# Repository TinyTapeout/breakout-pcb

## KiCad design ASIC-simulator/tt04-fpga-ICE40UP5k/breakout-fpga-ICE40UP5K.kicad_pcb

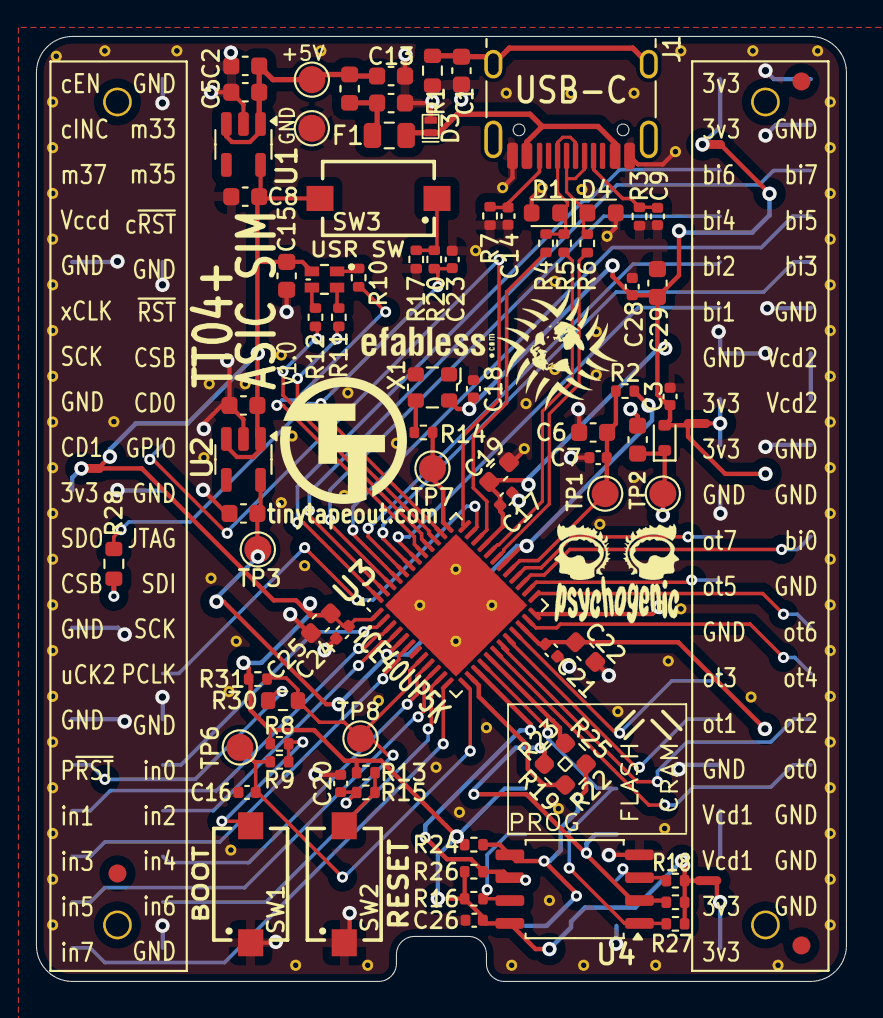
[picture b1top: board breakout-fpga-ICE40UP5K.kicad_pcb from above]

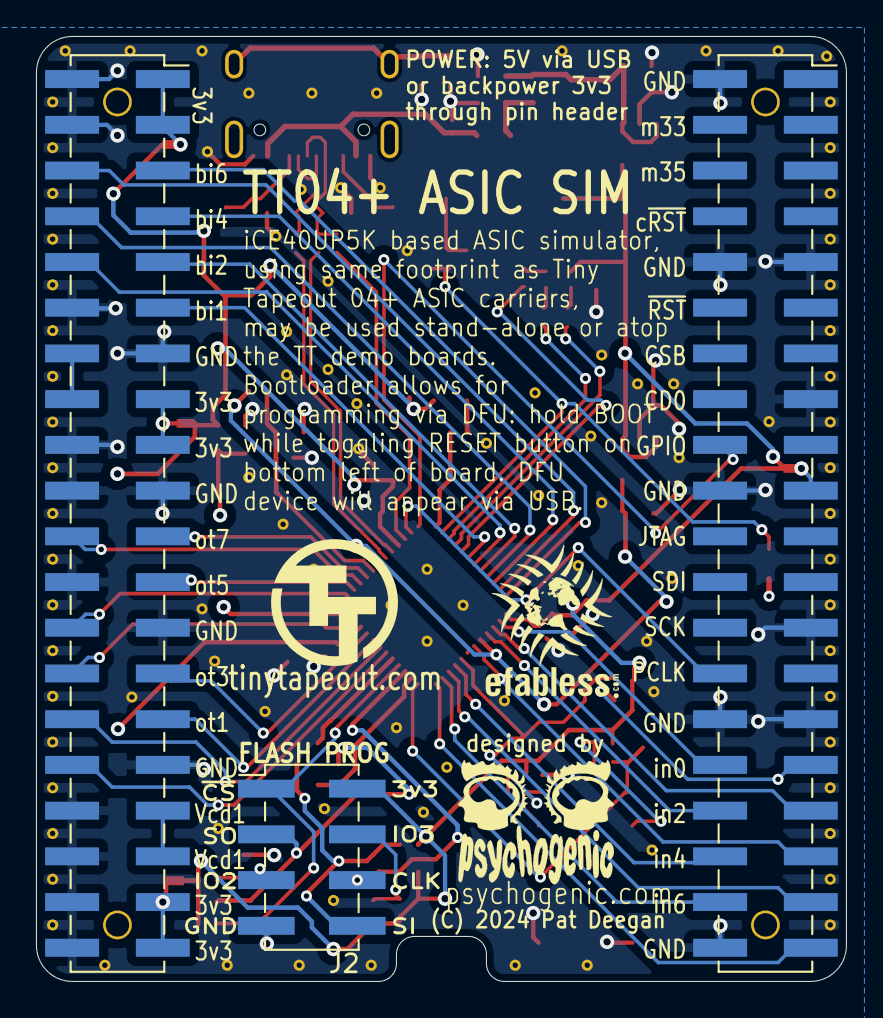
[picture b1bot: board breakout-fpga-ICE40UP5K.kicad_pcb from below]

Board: 4 copper layers, 45.0 x 52.5 mm, 191 parts (3 on the bottom side), 71 nets.

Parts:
C1: CUSBSHIELD; C_0603_1608Metric
C2, C4, C5, C8, C11, C12, C13: C_1u_0603_50V; C_0603_1608Metric
C3, C7, C16, C17, C18, C20, C21, C23, C24, C26, C28: C_100n_0402_50V; C_0402_1005Metric
C6, C10, C15, C19, C22, C25, C29: C_4p7u_0603_25V; C_0603_1608Metric
C9, C14: C_330p_0402_50V; C_0402_1005Metric
CON1, CON2: FH-00148_PinSocket_2x20_P2.54mm
D1, D4: TVS; D_0603_1608Metric
D2: 1N4448WT; D_SOD-523
D3: VBUSTVS; DFN1006-2
D5: RGB; LED_EAST1616RGBA3
F1: 350mA; Fuse_0805_2012Metric
FB1: 120R; L_0603_1608Metric
FID1, FID2, FID3: Fiducial; Fiducial_1mm_Mask2mm
J1: USB_C; USB_C_Receptacle_HRO_TYPE-C-31-M-12
J2: Conn_02x04_Odd_Even; PinHeader_2x04_P2.54mm_Vertical_SMD
NT1, NT2, NT3, NT4: NetTie_2; NetTie-2_SMD_Pad0.5mm
R1: R_1M_0603; R_0603_1608Metric
R2, R10, R14: R_100R_0402; R_0402_1005Metric
R3, R7: R_5k1_0402; R_0402_1005Metric
R4, R9, R15, R20: R_1k5_0402; R_0402_1005Metric
R5, R6, R11, R12: R_68R_0402; R_0402_1005Metric
R8, R13, R16, R17, R18, R21, R24, R26, R27, R31: R_10k_0402; R_0402_1005Metric
R19, R22, R23, R25, R28, R30: R_0R_0603_JUMPER; R_0603_1608Metric
STITCH1, STITCH1#2, STITCH1#3, STITCH1#4, STITCH1#5, STITCH1#6, STITCH1#7, STITCH1#8, STITCH1#9, STITCH1#10, STITCH1#11, STITCH1#12, STITCH1#13, STITCH1#14, STITCH1#15, STITCH1#16, STITCH1#17, STITCH1#18, STITCH1#19, STITCH1#20, STITCH1#21, STITCH1#22, STITCH1#23, STITCH1#24, STITCH1#25, STITCH1#26, STITCH1#27, STITCH1#28, STITCH1#29, STITCH1#30, STITCH1#31, STITCH1#32, STITCH1#33, STITCH1#34, STITCH1#35, STITCH1#36, STITCH1#37, STITCH1#38, STITCH1#39, STITCH1#40, STITCH1#41, STITCH1#42, STITCH1#43, STITCH1#44, STITCH2, STITCH3, STITCH4, STITCH5, STITCH6, STITCH7, STITCH8, STITCH9, STITCH10, STITCH11, STITCH12, STITCH13, STITCH14, STITCH15, STITCH17, STITCH18, STITCH19, STITCH20, STITCH21, STITCH22, STITCH23, STITCH24, STITCH25, STITCH26, STITCH27, STITCH28, STITCH29, STITCH30, STITCH31, STITCH32, STITCH33, STITCH34, STITCH35, STITCH36, STITCH37, STITCH38, STITCH39, STITCH40, STITCH43, STITCH44, STITCH46, STITCH47, STITCH48, STITCH50, STITCH51, STITCH52, STITCH54, STITCH59, STITCH60, STITCH61, STITCH62, STITCH62#2, STITCH62#3, STITCH62#4, STITCH62#5: StitchingVia-0.3mm
SW1, SW2, SW3: 434121025816
TP1, TP2, TP3, TP4, TP5, TP6, TP7, TP8: TestPoint; TestPoint_Pad_D1.5mm
U1: AP2112K-3.3; SOT-23-5
U2: AP2112K-1.2; SOT-23-5
U3: ICE40UP5K-SG48ITR; QFN-48-1EP_7x7mm_P0.5mm_EP5.6x5.6mm
U4: W25Q32JVSS; SOIC-8_5.23x5.23mm_P1.27mm
X1: 24MHz; Oscillator_SMD_ECS_2520MV-xxx-xx-4Pin_2.5x2.0mm

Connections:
+1V2: C11.1, R2.1, TP3.1, U2.5 (VOUT), U3.5 (VCC), U3.30 (VCC)
+2V5: C10.1, D2.1 (K), TP2.1, U3.24 (VPP_2V5)
+3V3: C3.1, C4.1, C8.1, C15.1, C17.1, C18.1, C19.1, C21.1, C22.1, C24.1, C25.1, C26.1, C28.1, C29.1, D2.2 (A), D5.4, J2.2, NT1.2, NT2.2, NT3.2, NT4.2, R8.1, R13.1, R16.1, R18.1, R21.1, R24.1, R26.1, R27.1, R31.1, SW3.2, U1.5 (VOUT), U2.1 (VIN), U2.3 (EN), U3.1 (VCCIO_2), U3.22 (SPI_VCCIO1), U3.33 (VCCIO_0), U4.8 (VCC), X1.4 (VDD)
+5V: C2.1, C5.1, C13.1, FB1.2, TP4.1, U1.1 (VIN), U1.3 (EN)
/CC1: C9.1, J1.A5 (CC1), R3.1
/CC2: C14.1, J1.B5 (CC2), R7.1
/FL_MISO: J2.3, R19.1, R21.2, R23.1, U4.2 (DO(IO1))
/FL_MOSI: J2.8, R22.2, R24.2, R25.2, U4.5 (DI(IO0))
/FPGA_SI: R23.2, R25.1, U3.17 (IOB_33b_SPI_SI)
/FPGA_SO: R19.2, R22.1, U3.14 (IOB_32a_SPI_SO)
/IOT_44B: R4.1, U3.34 (IOT_44b)
/LED_B: R12.2, U3.40 (RGB1)
/LED_G: R11.2, U3.39 (RGB0)
/LED_R: R10.2, U3.41 (RGB2)
/VCC_PLL: C6.1, C7.1, R2.2, TP1.1, U3.29 (VCCPLL)
/fl_io2: J2.5, R18.2, U4.3 (IO2)
/fl_io3: J2.4, R16.2, U4.7 (IO3)
/oscclk: R14.1, X1.3 (OUT)
/spi_clk: J2.6, R26.2, U3.15 (IOB_34a_SPI_SCK), U4.6 (CLK)
/vbus: D3.1 (K), F1.1, J1.A4 (VBUS), J1.A9 (VBUS), J1.B4 (VBUS), J1.B9 (VBUS)
/vbusfused: C12.1, F1.2, FB1.1
/~FLCS: J2.1, R27.2, U3.16 (IOB_35b_SPI_SS), U4.1 (~CS)
BOOT: C16.1, R9.2, TP6.1, U3.13 (IOB_24a)
GND: C1.2, C2.2, C3.2, C4.2, C5.2, C6.2, C7.2, C8.2, C9.2, C10.2, C11.2, C12.2, C13.2, C14.2, C15.2, C16.2, C17.2, C18.2, C19.2, C20.2, C21.2, C22.2, C23.2, C24.2, C25.2, C26.2, C28.2, C29.2, CON1.2, CON1.9, CON1.10, CON1.15, CON1.20, CON1.25, CON1.29, CON1.30, CON1.40, CON2.2, CON2.4, CON2.12, CON2.13, CON2.18, CON2.19, CON2.20, CON2.24, CON2.25, CON2.31, CON2.34, CON2.36, CON2.38, CON2.40, D1.2 (A2), D3.2 (A), D4.2 (A2), J1.A1 (GND), J1.A12 (GND), J1.B1 (GND), J1.B12 (GND), J2.7, R1.2, R3.2, R7.2, R17.2, STITCH1.1, STITCH1#2.1, STITCH1#3.1, STITCH1#4.1, STITCH1#5.1, STITCH1#6.1, STITCH1#7.1, STITCH1#8.1, STITCH1#9.1, STITCH1#10.1, STITCH1#11.1, STITCH1#12.1, STITCH1#13.1, STITCH1#14.1, STITCH1#15.1, STITCH1#16.1, STITCH1#17.1, STITCH1#18.1, STITCH1#19.1, STITCH1#20.1, STITCH1#21.1, STITCH1#22.1, STITCH1#23.1, STITCH1#24.1, STITCH1#25.1, STITCH1#26.1, STITCH1#27.1, STITCH1#28.1, STITCH1#29.1, STITCH1#30.1, STITCH1#31.1, STITCH1#32.1, STITCH1#33.1, STITCH1#34.1, STITCH1#35.1, STITCH1#36.1, STITCH1#37.1, STITCH1#38.1, STITCH1#39.1, STITCH1#40.1, STITCH1#41.1, STITCH1#42.1, STITCH1#43.1, STITCH1#44.1, STITCH2.1, STITCH3.1, STITCH4.1, STITCH5.1, STITCH6.1, STITCH7.1, STITCH8.1, STITCH9.1, STITCH10.1, STITCH11.1, STITCH12.1, STITCH13.1, STITCH14.1, STITCH15.1, STITCH17.1, STITCH18.1, STITCH19.1, STITCH20.1, STITCH21.1, STITCH22.1, STITCH23.1, STITCH24.1, STITCH25.1, STITCH26.1, STITCH27.1, STITCH28.1, STITCH29.1, STITCH30.1, STITCH31.1, STITCH32.1, STITCH33.1, STITCH34.1, STITCH35.1, STITCH36.1, STITCH37.1, STITCH38.1, STITCH39.1, STITCH40.1, STITCH43.1, STITCH44.1, STITCH46.1, STITCH47.1, STITCH48.1, STITCH50.1, STITCH51.1, STITCH52.1, STITCH54.1, STITCH59.1, STITCH60.1, STITCH61.1, STITCH62.1, STITCH62#2.1, STITCH62#3.1, STITCH62#4.1, STITCH62#5.1, SW1.1, SW2.1, TP5.1, U1.2 (GND), U2.2 (GND), U3.49 (GND), U4.4 (GND), X1.2 (GND)
unnamed: D5.1, R10.1
unnamed: D5.2, R11.1
unnamed: D5.3, R12.1
unnamed: C1.1, J1.S1 (SHIELD), R1.1
unnamed: R8.2, R9.1, SW1.2
unnamed: R13.2, R15.1, SW2.2
unnamed: R17.1, R20.1, SW3.1
USB_D+: D1.1 (A1), J1.A6 (D+), J1.B6 (D+), R4.2, R5.1
USB_D-: D4.1 (A1), J1.A7 (D-), J1.B7 (D-), R6.1
USB_DN: R6.2, U3.31 (IOT_42b)
USB_DP: R5.2, U3.32 (IOT_43a)
clk/mio[6]: CON1.28, U3.35 (IOT_46b_G0)
gpio: CON1.18, U3.36 (IOT_48b)
sys_clk: R14.2, TP7.1, U3.37 (IOT_45a_G1)
ui_in[0]/mio[8]: CON1.32, U3.2 (IOB_6a)
ui_in[1]/mio[9]: CON1.33, U3.3 (IOB_9b)
ui_in[2]/mio[10]: CON1.34, U3.4 (IOB_8a)
ui_in[3]/mio[11]: CON1.35, U3.6 (IOB_13b)
ui_in[4]/mio[12]: CON1.36, U3.9 (IOB_16a)
ui_in[5]/mio[13]: CON1.37, U3.10 (IOB_18a)
ui_in[6]/mio[14]: CON1.38, U3.11 (IOB_20a)
ui_in[7]/mio[15]: CON1.39, U3.12 (IOB_22a)
uio[0]/mio[24]: CON2.22, U3.27 (IOT_38b)
uio[1]/mio[25]: CON2.11, U3.42 (IOT_51a)
uio[2]/mio[26]: CON2.9, U3.44 (IOB_3b_G6)
uio[3]/mio[27]: CON2.10, U3.43 (IOT_49a)
uio[4]/mio[28]: CON2.7, U3.46 (IOB_0a)
uio[5]/mio[29]: CON2.8, U3.45 (IOB_5b)
uio[6]/mio[30]: CON2.5, U3.48 (IOB_4a)
uio[7]/mio[31]: CON2.6, U3.47 (IOB_2a)
uo_out[0]/mio[16]: CON2.32, U3.18 (IOB_31b)
uo_out[1]/mio[17]: CON2.29, U3.20 (IOB_25b_G3)
uo_out[2]/mio[18]: CON2.30, U3.19 (IOB_29b)
uo_out[3]/mio[19]: CON2.27, U3.21 (IOB_23b)
uo_out[4]/mio[20]: CON2.28, U3.23 (IOT_37a)
uo_out[5]/mio[21]: CON2.23, U3.26 (IOT_39a)
uo_out[6]/mio[22]: CON2.26, U3.25 (IOT_36b)
uo_out[7]/mio[23]: CON2.21, U3.28 (IOT_41a)
usr_sw1: C23.1, R20.2, R28.2, U3.38 (IOT_50b)
vccd1: CON2.33, CON2.35
vccd2: CON2.14, CON2.16
vdda: CON1.19, NT1.1
vdda1: CON2.37, CON2.39, NT2.1
vdda2: CON2.1, CON2.3, NT3.1
vddio: CON2.15, CON2.17, NT4.1
~CRESET: C20.1, R15.2, R30.2, R31.2, TP8.1, U3.8 (~CRESET)
~rst/mio[7]: CON1.31, R28.1, R30.1

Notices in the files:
ASIC-simulator/tt04-fpga-ICE40UP5k/breakout-fpga-ICE40UP5K.kicad_pcb:
(C) 2024 Pat Deegan
